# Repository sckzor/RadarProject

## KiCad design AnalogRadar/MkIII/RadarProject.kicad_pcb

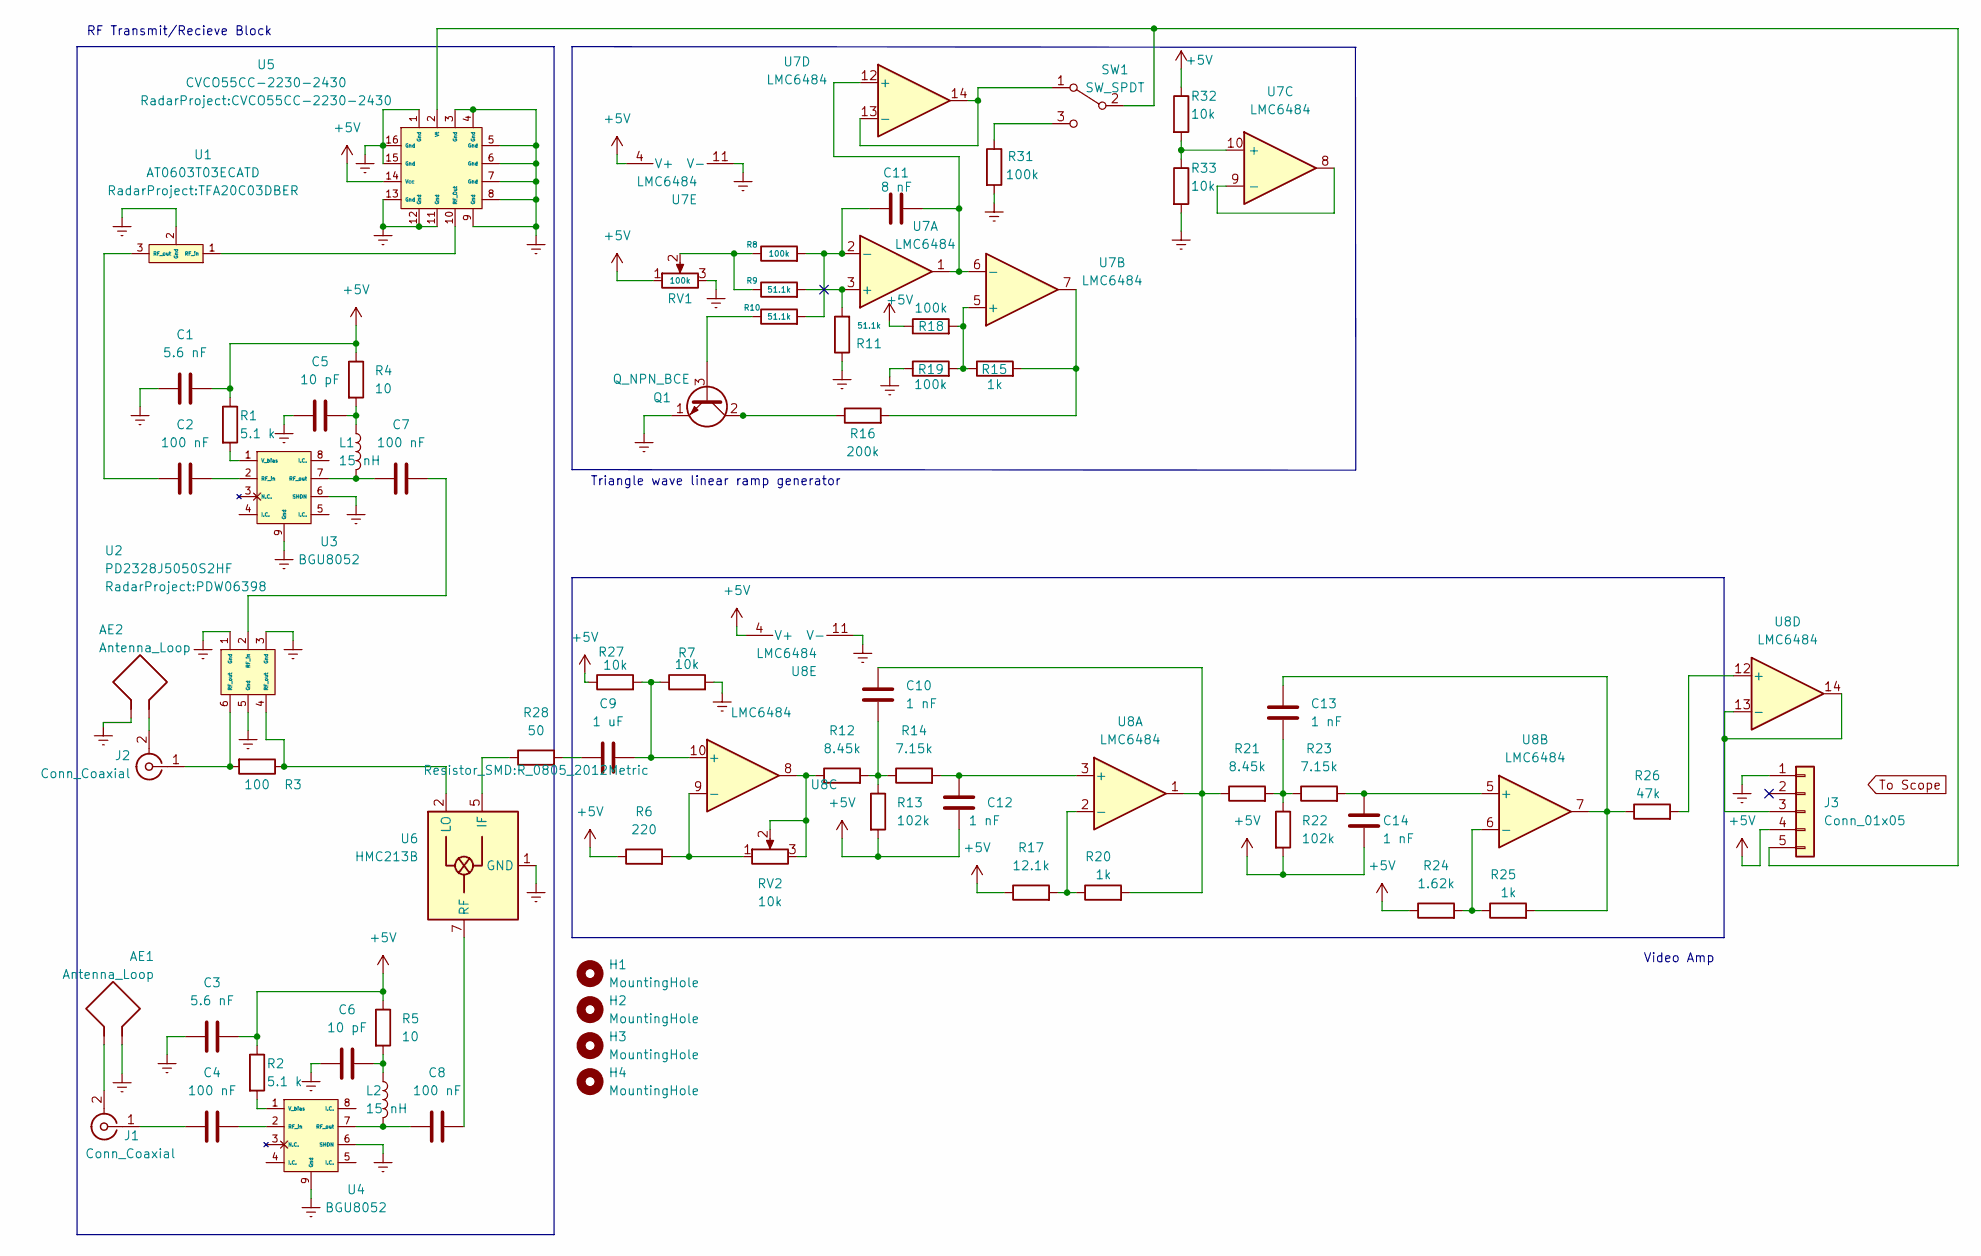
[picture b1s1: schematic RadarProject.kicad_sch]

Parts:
AE1, AE2: Antenna_Loop
C1, C3: 5.6 nF; C_0805_2012Metric
C2, C4, C7, C8: 100 nF; C_0805_2012Metric
C5, C6: 10 pF; C_0805_2012Metric
C9: 1 uF; C_0805_2012Metric
C10, C12, C13, C14: 1 nF; C_0805_2012Metric
C11: 8 nF; C_0805_2012Metric
H1, H2, H3, H4: MountingHole; MountingHole_2.7mm
J1, J2: Conn_Coaxial; SMA_Samtec_SMA-J-P-X-ST-EM1_EdgeMount
J3: Conn_01x05; PinHeader_1x05_P2.54mm_Vertical
L1, L2: 15 nH; L_0805_2012Metric
Q1: Q_NPN_BCE; TO-92L_Inline
R1, R2: 5.1 k; R_0805_2012Metric
R3: 100; R_0805_2012Metric
R4, R5: 10; R_0805_2012Metric
R6: 220; R_0805_2012Metric
R7, R27, R32, R33: 10k; R_0805_2012Metric
R8, R18, R19, R31: 100k; R_0805_2012Metric
R9, R10, R11: 51.1k; R_0805_2012Metric
R12, R21: 8.45k; R_0805_2012Metric
R13, R22: 102k; R_0805_2012Metric
R14, R23: 7.15k; R_0805_2012Metric
R15, R20, R25: 1k; R_0805_2012Metric
R16: 200k; R_0805_2012Metric
R17: 12.1k; R_0805_2012Metric
R24: 1.62k; R_0805_2012Metric
R26: 47k; R_0805_2012Metric
R28: 50; R_0805_2012Metric
RV1: 100k; Potentiometer_Bourns_3296W_Vertical
RV2: 10k; Potentiometer_Bourns_3296W_Vertical
SW1: SW_SPDT; SW_Slide_1P2T_CK_OS102011MS2Q
U1: AT0603T03ECATD; TFA20C03DBER
U2: PD2328J5050S2HF; PDW06398
U3, U4: BGU8052
U5: CVCO55CC-2230-2430
U6: HMC213B; MSOP-8_3x3mm_P0.65mm
U7: LMC6484; SOIC-14_3.9x8.7mm_P1.27mm
U8: LMC6484

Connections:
+5V: C1.2, C3.2, C12.2, C14.2, J3.4, R1.1, R2.1, R4.1, R5.1, R6.1, R13.2, R17.1, R18.1, R22.2, R24.1, R27.1, R32.1, RV1.1, U5.14 (Vcc), U7.4 (V+), U8.4 (V+)
Earth: AE1.1, AE2.1, C1.1, C3.1, C5.1, C6.1, J1.2 (Ext), J2.2 (Ext), J3.1, Q1.1 (E), R7.2, R11.1, R19.1, R31.2, R33.2, RV1.3, U1.2 (Gnd), U2.1 (Gnd), U2.3 (Gnd), U2.5 (Gnd), U3.6 (SHDN), U3.9 (Gnd), U4.6 (SHDN), U4.9 (Gnd), U5.1 (Gnd), U5.3 (Gnd), U5.4 (Gnd), U5.5 (Gnd), U5.6 (Gnd), U5.7 (Gnd), U5.8, U5.9 (Gnd), U5.11 (Gnd), U5.12 (Gnd), U5.13 (Gnd), U5.15 (Gnd), U5.16 (Gnd), U6.1 (GND), U6.3 (GND), U6.6 (GND), U6.8 (GND), U7.11 (V-), U8.11 (V-)
unnamed: AE1.2, J1.2 (Ext)
unnamed: AE2.2, J2.2 (Ext)
unnamed: C2.1, U1.3 (RF_out)
unnamed: C2.2, U3.2 (RF_in)
unnamed: C4.1, J1.1 (In)
unnamed: C4.2, U4.2 (RF_in)
unnamed: C5.2, L1.1, R4.2
unnamed: C6.2, L2.1, R5.2
unnamed: C7.1, L1.2, U3.7 (RF_out)
unnamed: C7.2, U2.2 (RF_in)
unnamed: C8.1, L2.2, U4.7 (RF_out)
unnamed: C8.2, U6.7 (RF)
unnamed: C9.1, R28.2
unnamed: C10.1, R20.2, R21.1, U8.1
unnamed: C10.2, R12.2, R13.1, R14.1
unnamed: C11.1, R8.2, R10.2, U7.2 (-)
unnamed: C11.2, U7.1, U7.6 (-), U7.12 (+)
unnamed: C12.1, R14.2, U8.3 (+)
unnamed: C13.1, R25.2, R26.1, U8.7
unnamed: C13.2, R21.2, R22.1, R23.1
unnamed: C14.1, R23.2, U8.5 (+)
unnamed: J2.1 (In), R3.2, U2.6 (RF_out)
unnamed: J3.3, U8.13 (-), U8.14
unnamed: J3.5, SW1.2 (B), U5.2 (Vt)
unnamed: Q1.2 (C), R16.1
unnamed: Q1.3 (B), R10.1
unnamed: R1.2, U3.1 (V_bias)
unnamed: R2.2, U4.1 (V_bias)
unnamed: R3.1, U2.4 (RF_out), U6.2 (LO)
unnamed: R6.2, RV2.1, U8.9 (-)
unnamed: C9.2, R7.1, R27.2, U8.10 (+)
unnamed: R8.1, R9.1, RV1.2
unnamed: R9.2, R11.2, U7.3 (+)
unnamed: R12.1, RV2.2, RV2.3, U8.8
unnamed: R15.1, R18.2, R19.2, U7.5 (+)
unnamed: R15.2, R16.2, U7.7
unnamed: R17.2, R20.1, U8.2 (-)
unnamed: R24.2, R25.1, U8.6 (-)
unnamed: R26.2, U8.12 (+)
unnamed: R31.1, SW1.3 (C)
unnamed: R32.2, R33.1, U7.10 (+)
unnamed: SW1.1 (A), U7.13 (-), U7.14
unnamed: U1.1 (RF_in), U5.10 (RF_Out)
unnamed: R28.1, U6.5 (IF)
unnamed: U7.8, U7.9 (-)

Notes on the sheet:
RF Transmit/Recieve Block
Triangle wave linear ramp generator
Video Amp

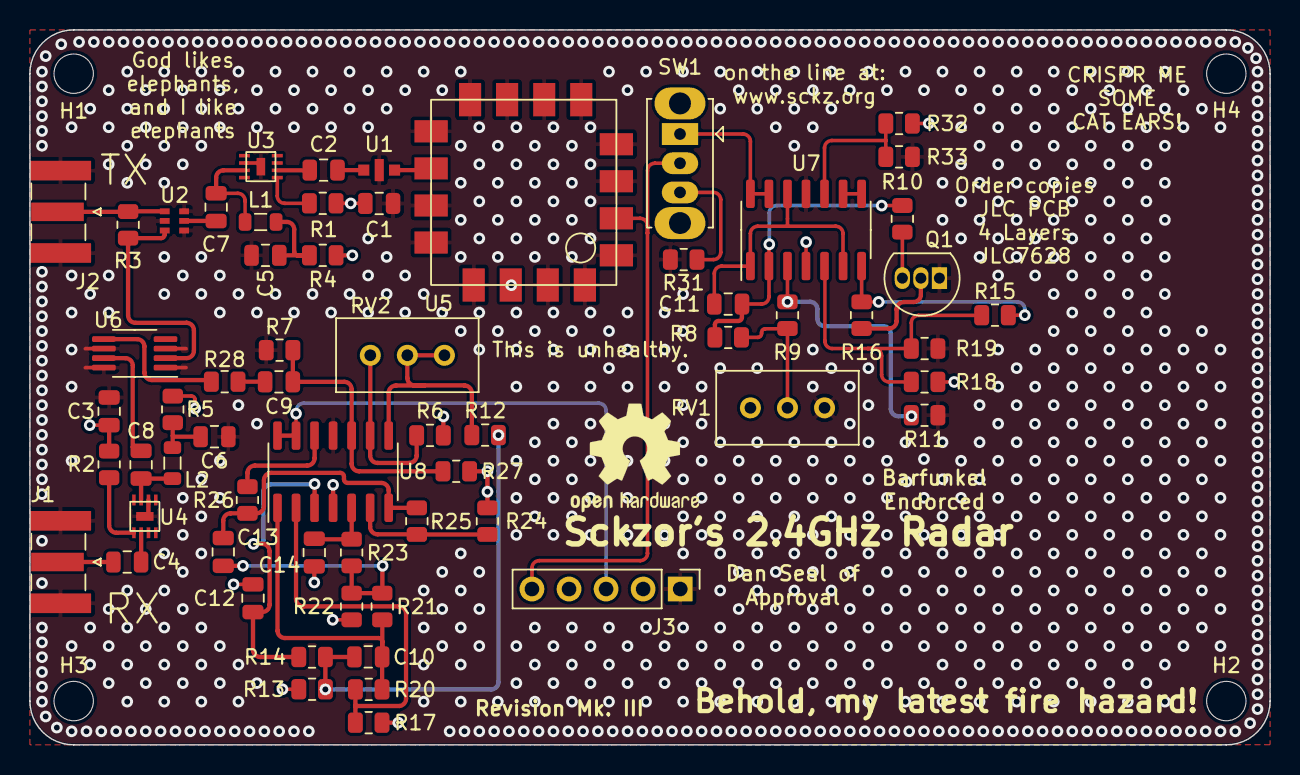
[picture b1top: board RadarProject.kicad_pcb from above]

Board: 4 copper layers, 85.0 x 49.0 mm, 66 parts (0 on the bottom side), 45 nets.

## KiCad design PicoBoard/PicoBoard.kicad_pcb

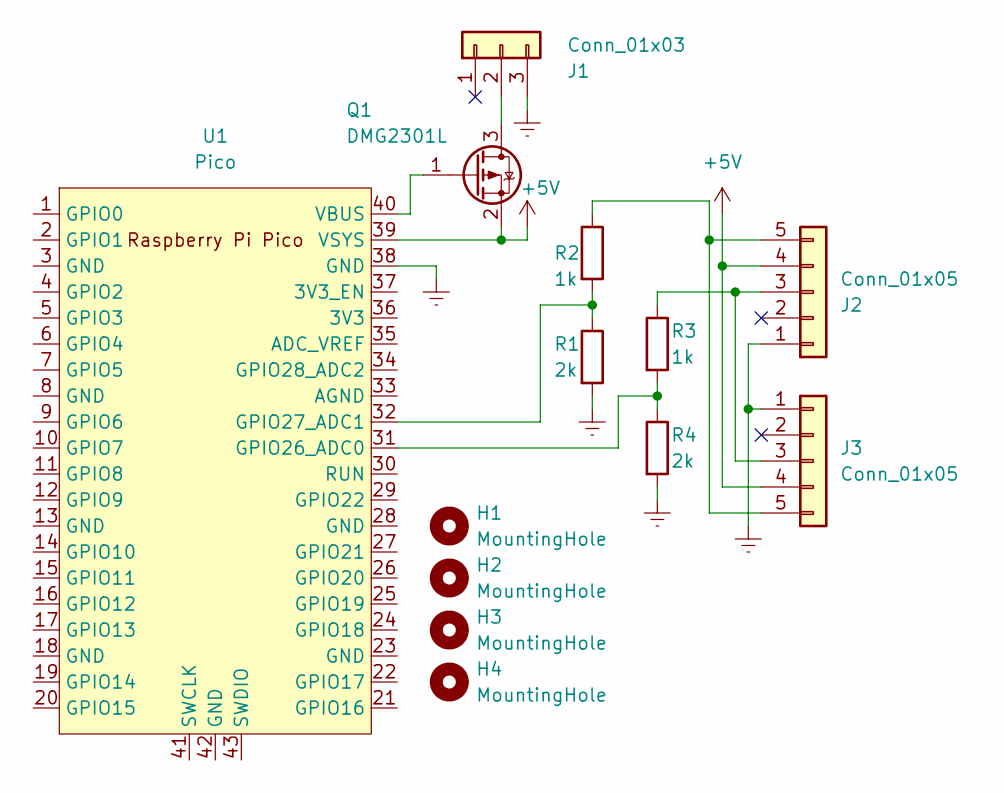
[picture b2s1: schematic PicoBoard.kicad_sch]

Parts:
H1, H2, H3, H4: MountingHole; MountingHole_2.7mm
J1: Conn_01x03; PinHeader_1x03_P2.54mm_Horizontal
J2: Conn_01x05; PinHeader_1x05_P2.54mm_Vertical
J3: Conn_01x05; PinHeader_1x05_P2.54mm_Horizontal
Q1: DMG2301L; SOT-23
R1, R4: 2k; R_0805_2012Metric
R2, R3: 1k; R_0805_2012Metric
U1: Pico; RPi_Pico_SMD_TH

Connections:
+5V: J2.4, J3.4, Q1.2 (S), U1.39 (VSYS)
Earth: J1.3, J2.1, J3.1, R1.2, R4.2, U1.38 (GND)
unnamed: J1.2, Q1.3 (D)
unnamed: J2.3, J3.3, R3.1
unnamed: J2.5, J3.5, R2.1
unnamed: Q1.1 (G), U1.40 (VBUS)
unnamed: R3.2, R4.1, U1.31 (GPIO26_ADC0)
unnamed: R1.1, R2.2, U1.32 (GPIO27_ADC1)

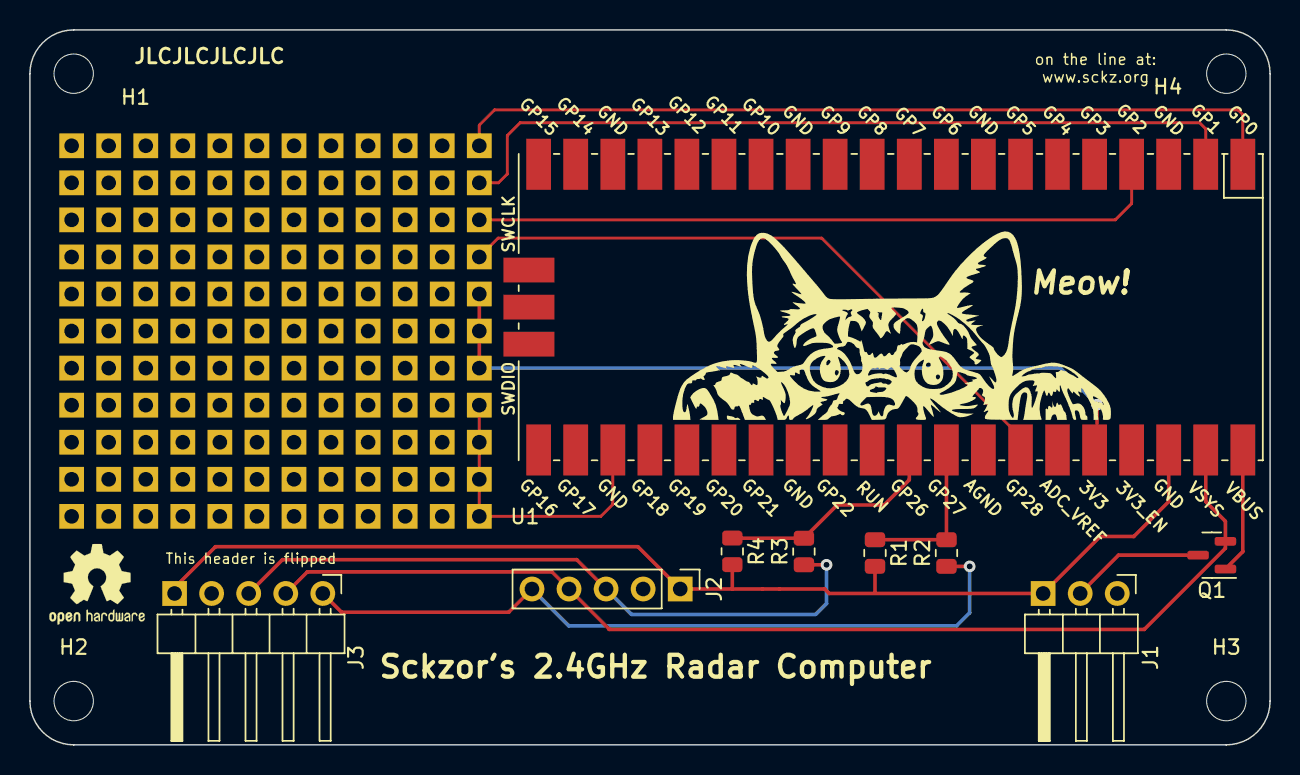
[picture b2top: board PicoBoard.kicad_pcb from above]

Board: 2 copper layers, 85.0 x 49.0 mm, 14 parts (0 on the bottom side), 8 nets.

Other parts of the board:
Meow!: LOGO

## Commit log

2022-09-07 Added all pcb files
2022-09-07 Redid directory structure
2022-09-07 removed usesless stuff
2022-09-11 Final schematic is generally done, just some minor fixes
2022-10-12 Updated PCB, added antennas, etc.
2022-10-12 Added shopping lists
2022-11-01 Final production PCB
2022-11-05 Added Raspberry Pi Pico bare metal code
2022-11-19 new version of PCB
2022-11-19 remade directory structure
2022-11-19 removed useless files
2022-11-19 changed directories more
2022-11-19 final commit for the rework
2022-11-20 added pico carrier board
2022-11-24 Create LICENSE
2022-11-24 final changes to pcb and code updates
2022-11-27 a bunch of usb stuff
2023-01-12 Added much better grounding an component spacing
2023-01-26 Updated PCB designs
2023-01-26 MkI info
